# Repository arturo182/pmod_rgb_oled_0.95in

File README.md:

# 0.95" OLED PMOD

A tiny color OLED!

Perfect solution if you need a small display with vivid, high-contrast 16-bit color. PMOD connector can be used with FPGA and MCU dev boards

The display itself is a 0.95" color OLED, the resolution is 96x64 RGB pixels.

The display is driven by the SSD1331 IC, you can control it with a 4-wire write-only SPI. The board only supports 3.3V logic.

Libraries exist to interface the PMOD:
- [Arduino library](https://github.com/adafruit/Adafruit-SSD1331-OLED-Driver-Library-for-Arduino)
- [CircuitPython library](https://github.com/adafruit/Adafruit_CircuitPython_SSD1331)

**Note: This module is not 5V-tolerant!**

Documentation licensed under the Creative Commons Attribution Share Alike 4.0 International License

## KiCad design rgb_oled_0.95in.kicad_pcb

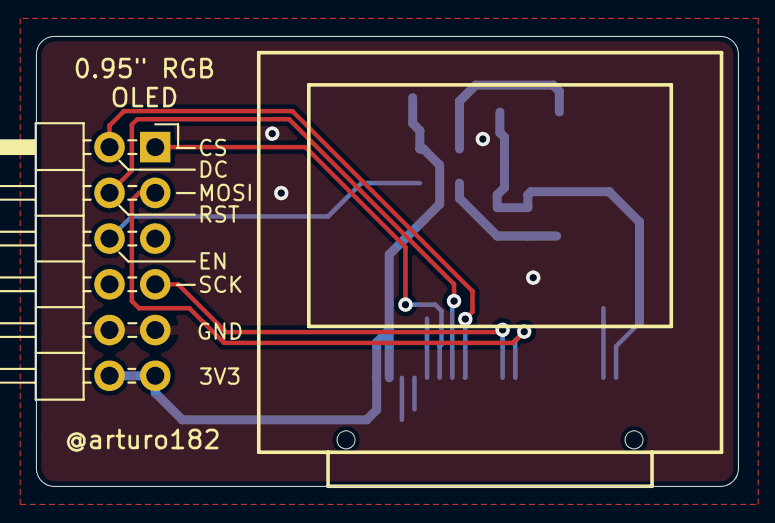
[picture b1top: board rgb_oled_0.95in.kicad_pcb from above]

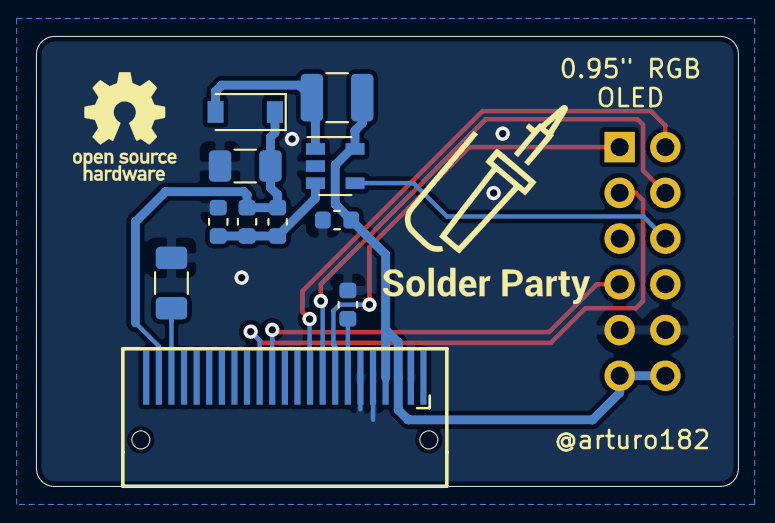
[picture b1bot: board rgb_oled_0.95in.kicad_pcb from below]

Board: 2 copper layers, 39.0 x 25.0 mm, 12 parts (10 on the bottom side), 13 nets.

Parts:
C1: 4.7uF; C_0603_1608Metric
C2: 0.1uF; C_0603_1608Metric
C3, C4: 4.7uF 16V; C_1206_3216Metric
D1: MBR0520LT1G; D_SOD-123
J1: PMOD; PMODHeader_2x06_P2.54mm_Horizontal
L1: 10uH, 0.48A; L_1210_3225Metric
R1: 147k; C_0603_1608Metric
R2: 13.3k; C_0603_1608Metric
R3: 510K; C_0603_1608Metric
U1: LMR62014; SOT-23-5
U2: UG-9664HDDAG01

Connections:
+3V3: C1.2, J1.6, J1.12, L1.1, U1.5, U2.3, U2.4
+15V: C2.2, C3.1, D1.1, R1.2, U2.22
/CS: J1.1, U2.8
/DC: J1.7, U2.10
/MOSI: J1.2, U2.14
/RESET: J1.8, U2.9
/SCK: J1.4, U2.13
/VDDEN: J1.9, U1.4
GND: C1.1, C3.2, C4.2, J1.5, J1.11, R2.1, R3.1, U1.2, U2.2, U2.5, U2.6
unnamed: C2.1, R1.1, R2.2, U1.3
unnamed: C4.1, U2.21
unnamed: D1.2, L1.2, U1.1
unnamed: R3.2, U2.7

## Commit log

2018-11-14 Initial import
2018-11-25 Add nicer silk
2018-11-25 Add bom
2019-05-11 Renamed bom, and schematic, added OLED 3d model
2019-05-11 Added README and images
2020-04-24 Add license
2020-04-24 Add more details and links to SW
2020-05-04 Update README.md
    Add a note about the license of the docs
